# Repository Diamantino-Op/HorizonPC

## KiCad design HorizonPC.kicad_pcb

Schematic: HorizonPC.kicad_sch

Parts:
BT1: ML641; BAT_1376164-1
C1, C2, C3, C21, C22, C23, C111, C188, C189, C190, C191: 47u; C_0805_2012Metric
C4, C17, C18, C19, C20, C24, C106, C107, C108, C110: 22u; C_0805_2012Metric
C5: 470n; C_0402_1005Metric
C6: 220n; C_0402_1005Metric
C7, C8, C9, C10: 2.2u; C_0402_1005Metric
C11, C14, C15, C16, C37, C104, C109: 1u; C_0402_1005Metric
C12, C13: 12p; C_0402_1005Metric
C25, C30, C35, C36, C38, C39, C40, C41, C44, C63, C64, C94, C105, C117, C118, C128, C129, C130, C131, C132, C133, C134, C135, C136, C137, C138, C139, C140, C141, C143, C144, C145, C146, C147, C148, C149, C150, C151, C152, C153, C154, C155, C156, C157, C158, C159, C160, C161, C162, C163, C164, C165, C166, C167, C168, C169, C170, C171, C173, C174, C175, C176, C179, C180, C181, C182, C183, C184, C185, C192, C194, C210, C211, C212, C213, C214, C215, C216, C217, C219, C220, C221, C222, C223, C224, C225, C226: 100n; C_0402_1005Metric
C26: 1n; C_0402_1005Metric
C27, C28, C29, C31, C32, C34: 10u; C_0402_1005Metric
C33, C93, C186, C187: 4.7u; C_0402_1005Metric
C42, C43, C120: 4.7n; C_0402_1005Metric
C60, C61, C68, C70, C71, C72, C73, C74, C75, C76, C77, C81, C82, C83, C85, C88, C89, C90, C196, C197, C198, C199, C200, C201, C202, C203, C204, C205, C207: 47n; C_0402_1005Metric
C112, C113, C114, C115: 10u; C_0805_2012Metric
C116: 1u; C_0805_2012Metric
C119: 100p; C_0402_1005Metric
C121: 10n; C_0402_1005Metric
D1, D2: NUP2105L; SOT-23
D3: 12V; D_SOD-123
D4, D6: CDSOD323-T05S; D_SOD-323
D5: CDSOD323-T03S; D_SOD-323
F1: 8A; Fuse_0603_1608Metric
J2: MSD-1-A; CUI_MSD-1-A
J3: Conn_01x05_Pin; PinHeader_1x05_P1.00mm_Vertical
J4: DF40C-90DP-0.4V(51); HIROSE_DF40C-90DP-0.4V_51_
J5, J6: BK13H-30DP/2-0.35V05(895); BK13H-30DP_2-0.35V05
JP1: BSCANP Jumper; SolderJumper-2_P1.3mm_Open_RoundedPad1.0x1.5mm
JP2: DEBUGEN Jumper; SolderJumper-2_P1.3mm_Open_RoundedPad1.0x1.5mm
L1, L2: 1u; L_1008_2520Metric
L3, L4: 1u; L_Changjiang_FTC201607S
L5, L6: ACT45B-510-2P-TL003; FIL_ACT45B-510-2P-TL003
L7: 4.7u; L_Changjiang_FXL1050
Q1: PMOS; PowerPAK_SO-8_Single
R1: 200k; R_0402_1005Metric
R2, R3, R6, R7, R9, R10, R11, R18, R19, R20, R21, R22, R23, R24, R25, R26, R27, R28, R37, R39, R40, R78, R79, R80, R81, R83, R84, R85, R87, R89, R90, R91, R92, R93: 10k; R_0402_1005Metric
R4, R5: 4.7k; R_0402_1005Metric
R8, R69, R70, R72, R88: 100k; R_0402_1005Metric
R29, R30, R31, R32: 60; R_0402_1005Metric
R38: 100; R_0402_1005Metric
R41, R42, R66: 240; R_0402_1005Metric
R71: 49.9k; R_0402_1005Metric
R73: 31.6k; R_0402_1005Metric
R74: 8m; R_1206_3216Metric
R75, R76: 10; R_0402_1005Metric
R77: 15k; R_0402_1005Metric
R82: 22; R_0402_1005Metric
R86: 1.8k; R_0402_1005Metric
R94: 47k; R_0402_1005Metric
RN1, RN2, RN3, RN4, RN5, RN6, RN7: 49.9; RESCAXS50P200X100X55-8N
SW1: 219-5LPSTR; SW_DIP_SPSTx05_Slide_6.7x14.26mm_W6.73mm_P2.54mm_LowProfile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
TP1: TestPoint; TestPoint_Pad_D1.0mm
U1: R9A07G043F05GBG#BC0; Manufacturer_Part_Number R9A07G043F05GBG#BC0
U2: TPS51200DRC; VSON-10-1EP_3x3mm_P0.5mm_EP1.65x2.4mm
U3: S25FL256SAGNFI011; WDFN-8-1EP_8x6mm_P1.27mm_EP6x4.8mm
U4: DA9062-52AM1; VQFN-40-1EP_6x6mm_P0.5mm_EP3.5x3.5mm
U5, U6: ATA6561-GBQW-N; VDFN8_3X3_MCH
U7: SM662GXC; BGA-100_14x18mm_Layout10x17_P1mm
U8: PUSB3TB6AZ; XSON7_PUSB3_NEX
U9, U10: ECMF02-2AMX6; ST_UQFN-6L_1.5x1.7mm_P0.5mm
U11: TPS552892RYQR; CONV_TPS552892RYQR
U12: TPS2051CDBV; SOT-23-5
U14, U15: DDR4; FBGA-96_9x14mm_Layout9x16_P0.8mm
Y1: 32.768KHz; Crystal_SMD_MicroCrystal_CC8V-T1A-2Pin_2.0x1.2mm
Y2: DSC6101JE3B-24MHz; Oscillator_SMD_Abracon_ASDMB-4Pin_2.5x2.0mm

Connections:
+1.1V: C1.1, C21.1, C128.2, C129.2, C130.2, C131.2, C138.1, C140.1, C143.1, C144.1, C145.1, C146.1, C166.2, C186.1, L1.2, U1.K10 (VDD), U1.K12 (VDD), U1.K14 (VDD), U1.K16 (VDD), U1.L11 (VDD), U1.L13 (VDD), U1.L15 (VDD), U1.M10 (VDD), U1.M12 (VDD), U1.M14 (VDD), U1.M16 (VDD), U1.N11 (VDD), U1.N13 (VDD), U1.N15 (VDD), U1.P10 (VDD), U1.P12 (VDD), U1.P14 (VDD), U1.P16 (VDD), U1.R11 (VDD), U1.R13 (VDD), U1.R15 (VDD), U1.T6 (PLL23_DVDD11), U1.T10 (VDD), U1.T12 (VDD), U1.T14 (VDD), U1.T16 (VDD), U1.Y15 (PLL5_DVDD11), U4.26 (VBUCK1)
+1.2V: C2.1, C22.1, C31.2, C32.2, C60.2, C61.1, C68.2, C70.2, C71.1, C72.1, C73.1, C75.1, C76.2, C77.1, C81.2, C82.1, C83.2, C85.2, C171.1, C173.1, C174.1, C175.1, C176.1, C192.1, C194.1, C196.2, C197.1, C198.2, C199.1, C200.2, C201.1, C202.2, C203.2, C204.1, C205.2, C207.2, L2.2, R9.2, U1.H20 (DDR_VDDQ), U1.K20 (DDR_VDDQ), U1.M20 (DDR_VDDQ), U1.R20 (DDR_VDDQ), U1.U20 (DDR_VDDQ), U1.W20 (DDR_VDDQ), U2.2 (VLDOIN), U4.27 (VBUCK2), U14.A1 (V_{DDQ}), U14.A9 (V_{DDQ}), U14.B3 (V_{DD}), U14.B9 (V_{DD}), U14.C1 (V_{DDQ}), U14.D1 (V_{DD}), U14.D9 (V_{DDQ}), U14.F2 (V_{DDQ}), U14.F8 (V_{DDQ}), U14.G1 (V_{DDQ}), U14.G7 (V_{DD}), U14.G9 (V_{DDQ}), U14.J1 (V_{DD}), U14.J2 (V_{DDQ}), U14.J8 (V_{DDQ}), U14.J9 (V_{DD}), U14.L1 (V_{DD}), U14.L9 (V_{DD}), U14.R1 (V_{DD}), U14.T9 (V_{DD}), U15.A1 (V_{DDQ}), U15.A9 (V_{DDQ}), U15.B3 (V_{DD}), U15.B9 (V_{DD}), U15.C1 (V_{DDQ}), U15.D1 (V_{DD}), U15.D9 (V_{DDQ}), U15.F2 (V_{DDQ}), U15.F8 (V_{DDQ}), U15.G1 (V_{DDQ}), U15.G7 (V_{DD}), U15.G9 (V_{DDQ}), U15.J1 (V_{DD}), U15.J2 (V_{DDQ}), U15.J8 (V_{DDQ}), U15.J9 (V_{DD}), U15.L1 (V_{DD}), U15.L9 (V_{DD}), U15.R1 (V_{DD}), U15.T9 (V_{DD})
+1.8V: C4.1, C24.1, C44.1, C132.1, C133.1, C134.2, C135.2, C136.1, C137.2, C141.1, C150.1, C151.1, C163.1, C219.2, C220.1, C221.2, C222.1, C223.2, C224.1, C225.2, C226.1, L4.2, U1.AC4 (USB_VDD18), U1.AC5 (USB_VDD18), U1.AC9 (USB_VDD18), U1.F11 (PLL6_AVDD18), U1.F17 (ADC_AVDD18), U1.G3 (SD0_PVDD), U1.L3 (PLL1_AVDD18), U1.N17 (PLL4_AVDD18), U1.P6 (VDD18), U1.U3 (PLL23_AVDD18), U1.Y11 (CSI_VDD18), U1.Y12 (CSI_VDD18), U1.Y14 (PLL5_AVDD18), U4.24 (VBUCK4), U7.H3 (VCCQ), U7.H8 (VCCQ), U7.L2 (VCCQ), U7.L4 (VCCQ), U7.L7 (VCCQ), U7.L9 (VCCQ), U7.P3 (VCCQ), U7.P8 (VCCQ)
+3.3V: C3.1, C23.1, C25.1, C33.1, C34.1, C35.1, C38.2, C40.2, C139.2, C160.1, C161.1, C164.1, C179.1, C180.1, C181.1, C182.1, C183.1, C184.1, C185.1, C187.2, C210.2, C211.2, C212.2, C213.2, C214.1, C215.1, C216.1, C217.1, JP2.2 (B), L3.2, R3.1, R4.1, R5.1, R7.1, R8.1, R11.1, R18.1, R79.1, R80.1, R81.1, R83.1, R87.1, R89.1, R90.1, R91.1, R92.1, R93.1, SW1.6, SW1.7, SW1.8, SW1.9, SW1.10, U1.C8 (SPI_PVDD), U1.C19 (PVDD), U1.F9 (PVDD), U1.F13 (PVDD), U1.F19 (PVDD), U1.W6 (PVDD), U1.Y7 (USB_VDD33), U1.Y8 (USB_VDD33), U1.Y10 (PVDD), U1.Y17 (PVDD_ETH1), U1.Y18 (PVDD), U2.7 (EN), U2.10 (VIN), U3.8 (VCC), U4.23 (VDDIO), U4.25 (VBUCK3), U5.5 (VIO), U6.5 (VIO), U7.F2 (VCC), U7.F3 (VCC), U7.F4 (VCC), U7.F5 (VCC), U7.F6 (VCC), U7.F7 (VCC), U7.F8 (VCC), U7.F9 (VCC), Y2.4 (VDD)
+5V: C14.1, C15.1, C16.1, C17.1, C18.1, C19.1, C20.1, C39.2, C41.2, C109.2, C155.2, D6.1 (A1), J6.8b, J6.9a, J6.9b, J6.10a, J6.10b, J6.11a, J6.11b, R2.1, R6.1, R72.1, R74.2, R76.2, U4.3 (VDD_LDO2), U4.10 (VDD_LDO34), U4.18 (VDD_BUCK4), U4.19 (VDD_BUCK3), U4.32 (VDD_BUCK1), U4.33 (VDD_BUCK2), U4.40 (VSYS), U5.3 (VCC), U6.3 (VCC), U12.5 (IN)
+5V_EXT: U1.AD8 (USB0_VBUSIN)
+5V_USB: C188.1, C189.1, C190.1, C191.1, D4.1 (A1), J6.5a, J6.5b, J6.6a, J6.6b, J6.7a, J6.7b, J6.8a, U12.1 (OUT)
ADC_CH0_ARM: J5.14a, U1.B18 (ADC_CH0)
ADC_CH1_ARM: J5.15a, U1.A18 (ADC_CH1)
ADC_TRG: U1.AC17 (ADC_TRG)
AUDIO_BCK: U1.AD18 (SSI3_BCK)
AUDIO_MCK: J5.4a, U1.B8 (AUDIO_CLK2)
AUDIO_RCK: U1.AC20 (SSI3_RCK)
AUDIO_RXD: U1.AC19 (SSI3_RXD)
AUDIO_TXD: U1.AE21 (SSI3_TXD)
BOOT0: R28.1, SW1.1, U1.G6 (MD_BOOT0)
BOOT1: R27.1, SW1.2, U1.C5 (MD_BOOT1)
BOOT2: R26.1, SW1.3, U1.C4 (MD_BOOT2)
CAN0_CANH: D1.2 (K), J4.45a, L6.4
CAN0_CANL: D1.1 (K), J4.44a, L6.2
CAN0_RXD: U1.C12 (CAN0_RX), U5.4 (RXD)
CAN0_STBY: R37.1, U1.AC15 (P8_3), U5.8 (STBY)
CAN0_TXD: U1.A11 (CAN0_TX), U5.1 (TXD)
CAN1_CANH: D2.2 (K), J4.45b, L5.4
CAN1_CANL: D2.1 (K), J4.44b, L5.2
CAN1_RXD: U1.B13 (CAN1_RX), U6.4 (RXD)
CAN1_STBY: R40.1, U1.AC16 (P8_2), U6.8 (STBY)
CAN1_TXD: U1.C13 (CAN1_TX), U6.1 (TXD)
CSI_CLK+: J4.29a, U1.AD11 (CSI_CLK+)
CSI_CLK-: J4.28a, U1.AE11 (CSI_CLK-)
CSI_D0+: J4.32a, U1.AD12 (CSI_D0+)
CSI_D0-: J4.31a, U1.AE12 (CSI_D0-)
CSI_D1+: J4.26a, U1.AD10 (CSI_D1+)
CSI_D1-: J4.25a, U1.AE10 (CSI_D1-)
CSI_D2+: J4.35a, U1.AD13 (ADC_CH1)
CSI_D2-: J4.34a, U1.AE13 (ADC_CH0)
CSI_D3+: J4.22a, U1.AD9 (CSI_D3+)
CSI_D3-: J4.23a, U1.AE9 (CSI_D3-)
DDR_A0: RN4.1 (R1.1), U1.H25 (DDR_ADDR11), U14.P3 (A0), U15.P3 (A0)
DDR_A1: RN2.3 (R3.1), U1.C24 (DDR_ADDR3), U14.P7 (A1), U15.P7 (A1)
DDR_A2: RN2.1 (R1.1), U1.E24 (DDR_BA0), U14.R3 (A2), U15.R3 (A2)
DDR_A3: RN3.4 (R4.1), U1.D23 (DDR_ADDR13), U14.N7 (A3), U15.N7 (A3)
DDR_A4: RN4.4 (R4.1), U1.J24 (DDR_CAS#), U14.N3 (A4), U15.N3 (A4)
DDR_A5: RN2.2 (R2.1), U1.D25 (DDR_ADDR15), U14.P8 (A5), U15.P8 (A5)
DDR_A6: RN2.4 (R4.1), U1.H24 (DDR_RAS#), U14.P2 (A6), U15.P2 (A6)
DDR_A7: RN1.3 (R3.1), U1.C25 (DDR_ADDR2), U14.R8 (A7), U15.R8 (A7)
DDR_A8: RN3.3 (R3.1), U1.H23 (DDR_ADDR14), U14.R2 (A8), U15.R2 (A8)
DDR_A9: RN1.4 (R4.1), U1.B24 (DDR_ADDR9), U14.R7 (A9), U15.R7 (A9)
DDR_A10: RN4.3 (R3.1), U1.F23 (DDR_BA2), U14.M3 (A10/AP), U15.M3 (A10/AP)
DDR_A11: RN1.2 (R2.1), U1.A24 (DDR_ADDR7), U14.T2 (A11), U15.T2 (A11)
DDR_A12: RN5.4 (R4.1), U1.G25 (DDR_WE#), U14.M7 (A12/~BC), U15.M7 (A12/~BC)
DDR_A13: RN1.1 (R1.1), U1.B25 (DDR_ADDR5), U14.T8 (A13), U15.T8 (A13)
DDR_ACT: RN6.3 (R3.1), U1.L25 (DDR_ODT1), U14.L3 (~ACT), U15.L3 (~ACT)
DDR_BA0: RN3.1 (R1.1), U1.J25 (DDR_ADDR6), U14.N2 (BA0), U15.N2 (BA0)
DDR_BA1: RN3.2 (R2.1), U1.E25 (DDR_ADDR0), U14.N8 (BA1), U15.N8 (BA1)
DDR_BG0: RN6.2 (R2.1), U1.N23 (DDR_ADDR12), U14.M2 (BG0), U15.M2 (BG0)
DDR_CAS: RN4.2 (R2.1), U1.F25 (DDR_ADDR8), U14.M8 (A15/~CAS), U15.M8 (A15/~CAS)
DDR_CK+: R38.1, U1.P25 (DDR_CLK_P), U14.K7 (CK_t), U15.K7 (CK_t)
DDR_CK-: R38.2, U1.P24 (DDR_CLK_N), U14.K8 (CK_c), U15.K8 (CK_c)
DDR_CKE: RN7.2 (R2.1), U1.M25 (DDR_CKE), U14.K2 (CKE), U15.K2 (CKE)
DDR_CS0: RN5.1 (R1.1), U1.L24 (DDR_BA1), U14.L7 (~CS)
DDR_CS1: RN5.2 (R2.1), U1.M24 (DDR_ODT0), U15.L7 (~CS)
DDR_DQ0: U1.W24 (DDR_DQ1), U14.G2 (DQ0), U15.G2 (DQ0)
DDR_DQ1: U1.Y25 (DDR_DQ3), U14.F7 (DQ1), U15.F7 (DQ1)
DDR_DQ2: U1.T23 (DDR_DQ7), U14.H3 (DQ2), U15.H3 (DQ2)
DDR_DQ3: U1.U25 (DDR_DQ5), U14.H7 (DQ3), U15.H7 (DQ3)
DDR_DQ4: U1.T24 (DDR_DQ4), U14.H2 (DQ4), U15.H2 (DQ4)
DDR_DQ5: U1.T25 (DDR_DQ0), U14.H8 (DQ5), U15.H8 (DQ5)
DDR_DQ6: U1.R24 (DDR_DQ2), U14.J3 (DQ6), U15.J3 (DQ6)
DDR_DQ7: U1.R25 (DDR_DQ6), U14.J7 (DQ7), U15.J7 (DQ7)
DDR_DQ8: U1.AD23 (DDR_DQ12), U14.A3 (DQ8), U15.A3 (DQ8)
DDR_DQ9: U1.AE24 (DDR_DQ15), U14.B8 (DQ9), U15.B8 (DQ9)
DDR_DQ10: U1.AC24 (DDR_DQ14), U14.C3 (DQ10), U15.C3 (DQ10)
DDR_DQ11: U1.AD24 (DDR_DQ8), U14.C7 (DQ11), U15.C7 (DQ11)
DDR_DQ12: U1.AA23 (DDR_DQ13), U14.C2 (DQ12), U15.C2 (DQ12)
DDR_DQ13: U1.AD25 (DDR_DQ11), U14.C8 (DQ13), U15.C8 (DQ13)
DDR_DQ14: U1.AA24 (DDR_DQ9), U14.D3 (DQ14), U15.D3 (DQ14)
DDR_DQ15: U1.W23 (DDR_DQ10), U14.D7 (DQ15), U15.D7 (DQ15)
DDR_LDM: U1.U23 (DDR_DM0), U14.E7 (NF/~LDM/~LDBI), U15.E7 (NF/~LDM/~LDBI)
DDR_LDQS+: U1.V25 (DDR_DQS0_P), U14.G3 (LDQS_t), U15.G3 (LDQS_t)
DDR_LDQS-: U1.V24 (DDR_DQS0_N), U14.F3 (LDQS_c), U15.F3 (LDQS_c)
DDR_ODT0: RN5.3 (R3.1), U1.L23 (DDR_CS1#), U14.K3 (ODT)
DDR_ODT1: RN6.4 (R4.1), U1.N24 (DDR_CS0#), U15.K3 (ODT)
DDR_PWR_GOOD: R8.2, U2.9 (PGOOD)
DDR_RAS: RN6.1 (R1.1), U1.K25 (DDR_ADDR1), U14.L8 (A16/~RAS), U15.L8 (A16/~RAS)
DDR_RESET#: R39.1, U1.B23 (DDR_RESET#), U14.P1 (~RESET), U15.P1 (~RESET)
DDR_UDM: U1.Y24 (DDR_DM1), U14.E2 (NF/~UDM/~UDBI), U15.E2 (NF/~UDM/~UDBI)
DDR_UDQS+: U1.AB24 (DDR_DQS1_P), U14.B7 (UDQS_t), U15.B7 (UDQS_t)
DDR_UDQS-: U1.AB25 (DDR_DQS1_N), U14.A7 (UDQS_c), U15.A7 (UDQS_c)
DDR_WE: RN7.1 (R1.1), U1.K23 (DDR_ADDR4), U14.L2 (A14/~WE), U15.L2 (A14/~WE)
ETH_MDC: J4.9a, U1.T3 (ET0_MDC)
ETH_MDIO: J4.10a, U1.T2 (ET0_MDIO)
ETH_RXC: J4.18a, U1.N3 (ET0_RXC)
ETH_RXD0: J4.16a, U1.P2 (ET0_RXD0)
ETH_RXD1: J4.15a, U1.R3 (ET0_RXD1)
ETH_RXD2: J4.13a, U1.R2 (ET0_RXD2)
ETH_RXD3: J4.12a, U1.R1 (ET0_RXD3)
ETH_RX_CTL: J4.20a, U1.N1 (ET0_RX_CTL)
ETH_TXC: J4.18b, U1.M2 (ET0_TXC)
ETH_TXD0: J4.16b, U1.L1 (ET0_TXD0)
ETH_TXD1: J4.15b, U1.L2 (ET0_TXD1)
ETH_TXD2: J4.13b, U1.K1 (ET0_TXD2)
ETH_TXD3: J4.12b, U1.K2 (ET0_TXD3)
ETH_TX_CTL: J4.20b, U1.M1 (ET0_TX_CTL)
GND: BT1.2 (-), C1.2, C2.2, C3.2, C4.2, C5.2, C6.2, C7.2, C8.2, C9.2, C10.2, C11.2, C12.2, C13.2, C14.2, C15.2, C16.2, C17.2, C18.2, C19.2, C20.2, C21.2, C22.2, C23.2, C24.2, C25.2, C26.2, C27.2, C28.2, C29.2, C30.2, C31.1, C32.1, C33.2, C34.2, C35.2, C36.2, C37.2, C38.1, C39.1, C40.1, C41.1, C42.2, C43.2, C44.2, C60.1, C61.2, C68.1, C70.1, C71.2, C72.2, C73.2, C74.2, C75.2, C76.1, C77.2, C81.1, C82.2, C83.1, C85.1, C88.2, C89.2, C90.2, C93.2, C94.2, C104.1, C105.1, C106.1, C107.1, C108.1, C109.1, C110.1, C111.1, C112.1, C113.1, C114.1, C115.1, C116.1, C117.1, C119.2, C120.1, C121.2, C128.1, C129.1, C130.1, C131.1, C132.2, C133.2, C134.1, C135.1, C136.2, C137.1, C138.2, C139.1, C140.2, C141.2, C143.2, C144.2, C145.2, C146.2, C147.2, C148.2, C149.2, C150.2, C151.2, C152.2, C153.2, C154.1, C155.1, C156.1, C157.1, C158.1, C159.1, C160.2, C161.2, C162.2, C163.2, C164.2, C165.2, C166.1, C167.1, C168.2, C169.1, C170.2, C171.2, C173.2, C174.2, C175.2, C176.2, C179.2, C180.2, C181.2, C182.2, C183.2, C184.2, C185.2, C186.2, C187.1, C188.2, C189.2, C190.2, C191.2, C196.1, C197.2, C198.1, C199.2, C200.1, C201.2, C202.1, C203.1, C204.2, C205.1, C207.1, C210.1, C211.1, C212.1, C213.1, C214.2, C215.2, C216.2, C217.2, C219.1, C220.2, C221.1, C222.2, C223.1, C224.2, C225.1, C226.2, D1.3 (A), D2.3 (A), D4.2 (A2), D5.2 (A2), D6.2 (A2), J2.6 (VSS), J2.G1 (SHIELD), J2.G2 (SHIELD), J2.G3 (SHIELD), J2.G4 (SHIELD), J4.5a, J4.11a, J4.11b, J4.14a, J4.14b, J4.17a, J4.17b, J4.19a, J4.19b, J4.21a, J4.21b, J4.24a, J4.27a, J4.30a, J4.33a, J4.36a, J4.38a, J4.43a, J4.43b, J4.MP (MountPin), J5.P1 (MountPin), J5.P2 (MountPin), J6.12a, J6.12b, J6.13a, J6.13b, J6.14a, J6.14b, J6.15a, J6.15b, J6.P2 (MountPin), JP1.2 (B), R1.2, R10.2, R24.2, R25.2, R26.2, R27.2, R28.2, R37.2, R39.2, R40.2, R41.2, R42.2, R66.2, R69.2, R71.2, R73.2, R78.2, R84.2, R85.2, R86.1, R88.2, R94.2, U1.A1 (VSS), U1.A8 (VSS), U1.A25 (VSS), U1.AA3 (VSS), U1.AA25 (VSS), U1.AB1 (VSS), U1.AB23 (VSS), U1.AC6 (VSS), U1.AC7 (VSS), U1.AC10 (VSS), U1.AC11 (VSS), U1.AC12 (VSS), U1.AC13 (VSS), U1.AC14 (VSS), U1.AC21 (VSS), U1.AC22 (VSS), U1.AC23 (VSS), U1.AC25 (VSS), U1.AD4 (VSS), U1.AD7 (VSS), U1.AD14 (VSS), U1.AD21 (VSS), U1.AD22 (VSS), U1.AE1 (VSS), U1.AE4 (VSS), U1.AE7 (VSS), U1.AE8 (VSS), U1.AE14 (VSS), U1.AE23 (VSS), U1.AE25 (VSS), U1.C18 (VSS), U1.C22 (VSS), U1.C23 (VSS), U1.D24 (VSS), U1.E23 (VSS), U1.F6 (VSS), U1.F7 (VSS), U1.F8 (VSS), U1.F10 (VSS), U1.F12 (VSS), U1.F15 (VSS), U1.F18 (VSS), U1.F24 (VSS), U1.G20 (VSS), U1.G23 (VSS), U1.G24 (VSS), U1.H1 (VSS), U1.J6 (VSS), U1.J9 (VSS), U1.J11 (VSS), U1.J13 (VSS), U1.J15 (VSS), U1.J17 (VSS), U1.J20 (VSS), U1.J23 (VSS), U1.K24 (VSS), U1.L6 (VSS), U1.L9 (VSS), U1.L17 (VSS), U1.L20 (VSS), U1.M23 (VSS), U1.N6 (VSS), U1.N9 (VSS), U1.N20 (VSS), U1.N25 (VSS), U1.P20 (VSS), U1.R6 (VSS), U1.R9 (VSS), U1.R17 (VSS), U1.R23 (VSS), U1.T1 (VSS), U1.T20 (VSS), U1.U6 (VSS), U1.U9 (VSS), U1.U11 (VSS), U1.U13 (VSS), U1.U15 (VSS), U1.U17 (VSS), U1.U24 (VSS), U1.V3 (VSS), U1.V6 (VSS), U1.V20 (VSS), U1.V23 (VSS), U1.W3 (VSS), U1.W25 (VSS), U1.Y1 (VSS), U1.Y2 (XIN), U1.Y6 (VSS), U1.Y9 (VSS), U1.Y13 (VSS), U1.Y16 (VSS), U1.Y20 (VSS), U1.Y23 (VSS), U2.4 (GND), U2.8 (GND), U2.11 (GND), U3.4 (GND), U3.9 (GND), U4.7 (GND), U4.41 (GND), U5.2 (GND), U5.9 (GND), U6.2 (GND), U6.9 (GND), U7.G2 (VSS), U7.G3 (VSS), U7.G4 (VSS), U7.G5 (VSS), U7.G6 (VSS), U7.G7 (VSS), U7.G8 (VSS), U7.G9 (VSS), U7.H2 (VSSQ), U7.H9 (VSSQ), U7.J5 (VSS), U7.L3 (VSSQ), U7.L8 (VSSQ), U7.M4 (VSSQ), U7.M7 (VSSQ), U7.P2 (VSSQ), U7.P9 (VSSQ), U8.1 (GND), U9.3 (GND), U10.3 (GND), U11.9 (GND), U11.17 (GND), U12.2 (GND), U14.A2 (V_{SSQ}), U14.A8 (V_{SSQ}), U14.B2 (V_{SS}), U14.C9 (V_{SSQ}), U14.D2 (V_{SSQ}), U14.D8 (V_{SSQ}), U14.E1 (V_{SS}), U14.E3 (V_{SSQ}), U14.E8 (V_{SSQ}), U14.E9 (V_{SS}), U14.F1 (V_{SSQ}), U14.G8 (V_{SS}), U14.H1 (V_{SSQ}), U14.H9 (V_{SSQ}), U14.K1 (V_{SS}), U14.K9 (V_{SS}), U14.M9 (V_{SS}), U14.N1 (V_{SS}), U14.T1 (V_{SS}), U15.A2 (V_{SSQ}), U15.A8 (V_{SSQ}), U15.B2 (V_{SS}), U15.C9 (V_{SSQ}), U15.D2 (V_{SSQ}), U15.D8 (V_{SSQ}), U15.E1 (V_{SS}), U15.E3 (V_{SSQ}), U15.E8 (V_{SSQ}), U15.E9 (V_{SS}), U15.F1 (V_{SSQ}), U15.G8 (V_{SS}), U15.H1 (V_{SSQ}), U15.H9 (V_{SSQ}), U15.K1 (V_{SS}), U15.K9 (V_{SS}), U15.M9 (V_{SS}), U15.N1 (V_{SS}), U15.T1 (V_{SS}), Y2.2 (GND)
GPIO0_33: J4.37a, U1.AE15 (P8_0)
GPIO0_1833: U1.K6 (P2_1)
GPIO1_33: J5.7a, U1.B17 (P18_2)
GPIO1_1833: U1.M3 (P2_2)
GPIO2_33: J5.11a, U1.A17 (P18_1)
GPIO2_1833: U1.M6 (P2_3)
GPIO3_33: J5.4b, U1.F16 (P18_0)
GPIO3_1833: U1.N2 (P4_2)
GPIO4_33: J5.8a, U1.C20 (P18_3)
GPIO4_1833: U1.P1 (P4_5)
GPIO5_33: J5.3b, U1.B12 (P13_3)
GPIO6_33: J5.6a, U1.A4 (P24_1)
GPIO7_33: J5.10a, U1.A14 (P16_0)
GPIO8_33: J5.9a, U1.B14 (P16_1)
GPIO9_33: J5.2b, U1.A12 (P13_4)
IRQ0: J5.12a, U1.A13 (IRQ3)
IRQ1: U1.AD20 (IRQ4)
IRQ2: U1.AE18 (IRQ5)
IRQ3: J5.13a, U1.B22 (IRQ6)
IRQ4: J5.15b, U1.A21 (IRQ7)
JTAG_TCK: J3.2, J4.4b, U1.U2 (TCK/SWDCLK)
JTAG_TDI: J3.5, J4.1b, U1.W1 (TDI)
JTAG_TDO: J3.4, J4.2b, U1.V2 (TDO)
JTAG_TMS: J3.1, J4.5b, U1.U1 (TMS/SWDIO)
JTAG_TRST#: J3.3, J4.3b, U1.V1 (TRST#)
LDO2_EN: U1.B3 (P24_4), U4.22 (GPIO1)
LDO3_EN: U1.A3 (P24_3), U4.28 (GPIO2)
LDO4_EN: U1.B4 (P24_2), U4.29 (GPIO3)
MAIN_RESET: J4.8a, R6.2, U4.16 (~RESETREQ)
MAIN_SCL: J5.13b, U1.B19 (RIIC0_SCL)
MAIN_SDA: J5.14b, U1.B20 (RIIC0_SDA)
MTU0_A: U1.AC18 (MTU4_A)
MTU0_AB_DIS#: J5.3a, R91.2, U1.B9 (POE0#)
MTU0_B: U1.AE19 (MTU4_B)
MTU0_C: U1.AD19 (MTU4_C)
MTU0_CD_DIS#: J5.2a, R89.2, U1.C9 (POE4#)
MTU0_D: U1.AE20 (MTU4_D)
MTU1_A: J4.10b, U1.AD3 (MTU7_A)
MTU1_AB_DIS#: J5.1a, R92.2, U1.B10 (POE8#)
MTU1_B: J4.9b, U1.AC3 (MTU7_B)
MTU1_C: J4.8b, U1.AB2 (MTU7_C)
MTU1_CD_DIS#: J5.1b, R90.2, U1.A10 (POE10#)
MTU1_D: J4.7b, U1.AC1 (MTU7_D)
NMI: J4.6b, U1.AA2 (NMI)
unnamed: BT1.1 (+), C5.1, U4.12 (VBBAT)
unnamed: C42.1, R29.2, R30.1
unnamed: C43.1, R31.2, R32.1
unnamed: C120.2, R77.2
unnamed: D3.2 (A), Q1.2 (G), R94.1
unnamed: D3.1 (K), F1.1, Q1.3 (S)
unnamed: JP1.1 (A), R79.2, U1.Y19 (DEBUGEN)
unnamed: JP2.1 (A), R78.1, U1.AE22 (BSCANP)
unnamed: L2.1, U4.34 (VLX_BUCK2), U4.35 (VLX_BUCK2)
unnamed: R82.2, U1.Y3 (EXCLK)
unnamed: R81.2, U1.F20 (MD_CLKS)
unnamed: R85.1, U1.A22 (MD_OSCDRV0)
unnamed: R84.1, U1.C21 (MD_OSCDRV1)
unnamed: R66.1, U1.A23 (DDR_CALIBRATION)
unnamed: R86.2, U1.AC8 (USB_RREF)
unnamed: C26.1, R9.1, R10.1, U2.1 (REFIN)
unnamed: R1.1, U4.4 (IREF)
unnamed: TP1.1 (1_1), U4.36 (TP)
unnamed: C7.1, U4.39 (VDDCORE)
unnamed: L1.1, U4.31 (VLX_BUCK1)
unnamed: L3.1, U4.20 (VLX_BUCK3)
unnamed: L4.1, U4.17 (VLX_BUCK4)
unnamed: C6.1, U4.5 (VREF)
unnamed: C13.1, U4.6 (XTAL_IN), Y1.2
unnamed: C12.1, U4.8 (XTAL_OUT), Y1.1
unnamed: L6.3, R31.1, U5.7 (CANH)
unnamed: L6.1, R32.2, U5.6 (CANL)
unnamed: L5.3, R29.1, U6.7 (CANH)
unnamed: L5.1, R30.2, U6.6 (CANL)
unnamed: C37.1, U7.E4 (VDDI)
unnamed: C63.1, U11.20 (BOOT1)
unnamed: C64.1, U11.19 (BOOT2)
unnamed: C119.1, R77.1, U11.15 (COMP)
unnamed: R72.2, R73.1, U11.14 (FB)
unnamed: R71.1, U11.6 (FSW)
unnamed: C118.2, R76.1, U11.13 (ISN)
unnamed: C118.1, R75.1, U11.12 (ISP)
unnamed: R70.1, U11.2 (MODE)
unnamed: C63.2, L7.1, U11.8 (SW1)
unnamed: C64.2, L7.2, U11.10 (SW2)
unnamed: C121.1, U11.5 (SYNC)
unnamed: C93.1, C94.1, R70.2, U11.18 (VCC)
unnamed: C104.2, C105.2, C106.2, C107.2, C108.2, C110.2, C111.2, R74.1, R75.2, U11.11 (VOUT)
unnamed: R41.1, U14.F9 (ZQ)
unnamed: R42.1, U15.F9 (ZQ)
unnamed: R82.1, Y2.3 (Out)
unnamed: R83.2, Y2.1 (Standby)
PWR_CC: R80.2, U1.C11 (IRQ1), U11.4 (~CC)
PWR_GOOD: R93.2, U1.AD15 (IRQ2), U11.3 (PG)
PWR_IRQ: R3.2, U1.C10 (IRQ0), U4.37 (~IRQ)
PWR_ONKEY: J4.6a, R2.2, U4.15 (~ONKEY)
PWR_RESET: R7.2, U1.W2 (PRST#), U4.38 (~RESET)
PWR_SCL: R4.2, U1.A19 (RIIC1_SCL), U4.14 (SCL)
PWR_SDA: R5.2, U1.A20 (RIIC1_SDA), U4.13 (SDA)
PWR_WDT: U1.B2 (P24_0), U4.21 (GPIO0)
PWR_WDT_ERR: J5.5a, U1.A2 (WDT)
QSPI_CS: R11.2, U1.B5 (QSPI0_SSL), U3.1 (~CS)
QSPI_IO0: U1.C7 (QSPI0_IO0), U3.5 (IO0)
QSPI_IO1: U1.A5 (QSPI0_IO1), U3.2 (IO1)
QSPI_IO2: U1.B7 (QSPI0_IO2), U3.3 (IO2)
QSPI_IO3: U1.C6 (QSPI0_IO3), U3.7 (IO3)
QSPI_SCK: U1.B6 (QSPI0_SPCLK), U3.6 (SCK)
SD0_CLK: U1.G1 (SD0_CLK), U7.P6 (CLK)
SD0_CMD: U1.E2 (SD0_CMD), U7.P5 (CMD)
SD0_D0: U1.F1 (SD0_DATA0), U7.K2 (D0)
SD0_D1: U1.H3 (SD0_DATA1), U7.N2 (D1)
SD0_D2: U1.F2 (SD0_DATA2), U7.K3 (D2)
SD0_D3: U1.D2 (SD0_DATA3), U7.N3 (D3)
SD0_D4: U1.E1 (SD0_DATA4), U7.N8 (D4)
SD0_D5: U1.D1 (SD0_DATA5), U7.K8 (D5)
SD0_D6: U1.E3 (SD0_DATA6), U7.N9 (D6)
SD0_D7: U1.F3 (SD0_DATA7), U7.K9 (D7)
SD0_WP: R25.1, SW1.4, U1.C2 (SD0_WP)
SD0_~RST: U1.C1 (SD0_RST#), U7.M5 (RST#)
SD1_CLK: J2.5 (CLK), U1.G2 (SD1_CLK), U8.3 (CH2)
SD1_CMD: J2.3 (CMD), R21.2, U1.H6 (SD1_CMD), U8.6 (CH5)
SD1_D0: J2.7 (DAT0), R20.2, U1.H2 (SD1_DATA0), U8.5 (CH4)
SD1_D1: J2.8 (DAT1), R19.2, U1.J3 (SD1_DATA1), U8.4 (CH3)
SD1_D2: J2.1 (DAT2), R23.2, U1.J1 (SD1_DATA2), U8.7 (CH6)
SD1_D3: J2.2 (DAT3/CD), R22.2, U1.J2 (SD1_DATA3), U8.2 (CH1)
SD1_DET: J2.CD (DET), R18.2, U1.D3 (SD1_CD)
SD1_WP: R24.1, SW1.5, U1.C3 (SD1_WP)
SERIAL_CTS: U1.AD2 (SCIF2_CTS)
SERIAL_RTS: U1.AC2 (SCIF2_RTS)
SERIAL_RXD: U1.AE2 (SCIF2_RXD)
SERIAL_SCK: U1.AE3 (SCIF2_SCK)
SERIAL_TXD: U1.AD1 (SCIF2_TXD)
SPI0_CLK: J5.8b, U1.C14 (RSPI0_CLK)
SPI0_MISO: J5.6b, U1.B15 (RSPI0_MISO)
SPI0_MOSI: J5.7b, U1.C15 (RSPI0_MOSI)
SPI0_SSL: J5.5b, U1.A15 (RSPI0_SSL)
SPI1_CLK: J5.12b, U1.C16 (RSPI1_CLK)
SPI1_MISO: J5.10b, U1.A16 (RSPI1_MISO)
SPI1_MOSI: J5.11b, U1.B16 (RSPI1_MOSI)
SPI1_SSL: J5.9b, U1.C17 (RSPI1_SSL)
SPI2_CLK: J4.41a, U1.AE17 (RSPI2_CLK)
SPI2_MISO: J4.39a, U1.AD16 (RSPI2_MISO)
SPI2_MOSI: J4.42a, U1.AD17 (RSPI2_MOSI)
SPI2_SSL: J4.40a, U1.AE16 (RSPI2_SSL)
SYS_EN: J4.7a, R69.1, U4.30 (GPIO4), U11.1 (EN)
USB+: U1.AD5 (USB1_DP), U9.1 (D+_in)
USB-: U1.AE5 (USB1_DM), U9.2 (D-_in)
USB_EN: R88.1, U1.B11 (USB1_VBUSEN), U12.4 (EN)
USB_ESD+: J4.1a, U9.6 (D+_out)
USB_ESD-: J4.2a, U9.5 (D-_out)
USB_FLT: R87.2, U1.AB3 (USB1_OVRCUR), U12.3 (~FLT)
USB_MAIN+: U1.AD6 (USB0_DP), U10.2 (D-_in)
USB_MAIN-: U1.AE6 (USB0_DM), U10.1 (D+_in)
USB_MAIN_ESD+: J4.4a, U10.5 (D-_out)
USB_MAIN_ESD-: J4.3a, U10.6 (D+_out)
VETH: C8.1, C165.1, U1.P3 (PVDD_ETH0), U4.2 (VLDO2)
VGPIO: C9.1, U4.11 (VLDO4)
VMAIN: C112.2, C113.2, C114.2, C115.2, C116.2, C117.2, F1.2, U11.7 (VIN)
VMAIN_RAW: J6.1a, J6.1b, J6.2a, J6.2b, J6.3a, J6.3b, J6.4a, J6.4b, J6.P1 (MountPin), Q1.1 (D)
VPP: C11.1, C74.1, C88.1, C89.1, C90.1, U4.1 (VLDO1), U14.B1 (V_{PP}), U14.R9 (V_{PP}), U15.B1 (V_{PP}), U15.R9 (V_{PP})
VSD1: C10.1, C36.1, C162.1, D5.1 (A1), J2.4 (VDD), R19.1, R20.1, R21.1, R22.1, R23.1, U1.K3 (SD1_PVDD), U4.9 (VLDO3)
VTT: C27.1, C28.1, C29.1, C147.1, C148.1, C149.1, C152.1, C153.1, C154.2, C156.2, C157.2, C158.2, C159.2, C167.2, C168.1, C169.2, C170.1, RN1.5 (R4.2), RN1.6 (R3.2), RN1.7 (R2.2), RN1.8 (R1.2), RN2.5 (R4.2), RN2.6 (R3.2), RN2.7 (R2.2), RN2.8 (R1.2), RN3.5 (R4.2), RN3.6 (R3.2), RN3.7 (R2.2), RN3.8 (R1.2), RN4.5 (R4.2), RN4.6 (R3.2), RN4.7 (R2.2), RN4.8 (R1.2), RN5.5 (R4.2), RN5.6 (R3.2), RN5.7 (R2.2), RN5.8 (R1.2), RN6.5 (R4.2), RN6.6 (R3.2), RN6.7 (R2.2), RN6.8 (R1.2), RN7.5 (R4.2), RN7.6 (R3.2), RN7.7 (R2.2), RN7.8 (R1.2), U2.3 (VO), U2.5 (VOSNS)
VTT_REF: C30.1, C192.2, C194.2, U2.6 (REFOUT), U14.M1 (V_{REFCA}), U15.M1 (V_{REFCA})

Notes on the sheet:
Main Power -> 5V
USB
MPU DDR4
Power
CAN1
QSPI
DDR4 Terminations
MPU CSI
MPU MTU
Reverse Polarity
DDR4 Bank 1
MPU USB
A18 / B18 only active with G2UL AD13 / AE13 only active with Rz/Five
To LEDs
MPU ADC
MPU GPIO
MPU Serial
DDR Terminations
USB ESD
MicroSD
DDR3L
MPU QSPI
MPU I2C
To Connector
CAN0
MPU Ethernet
Main USB ESD
MPU Clocks
MPU MicroSD
JTAG Connector
MPU Power
MPU Interrupts
Switches
MPU JTAG
DDR4 Bank 0
CAN
PMIC
MPU SPI
With G2UL: AE13 = CSI_D2- AD13 = CSI_D2+
eMMC

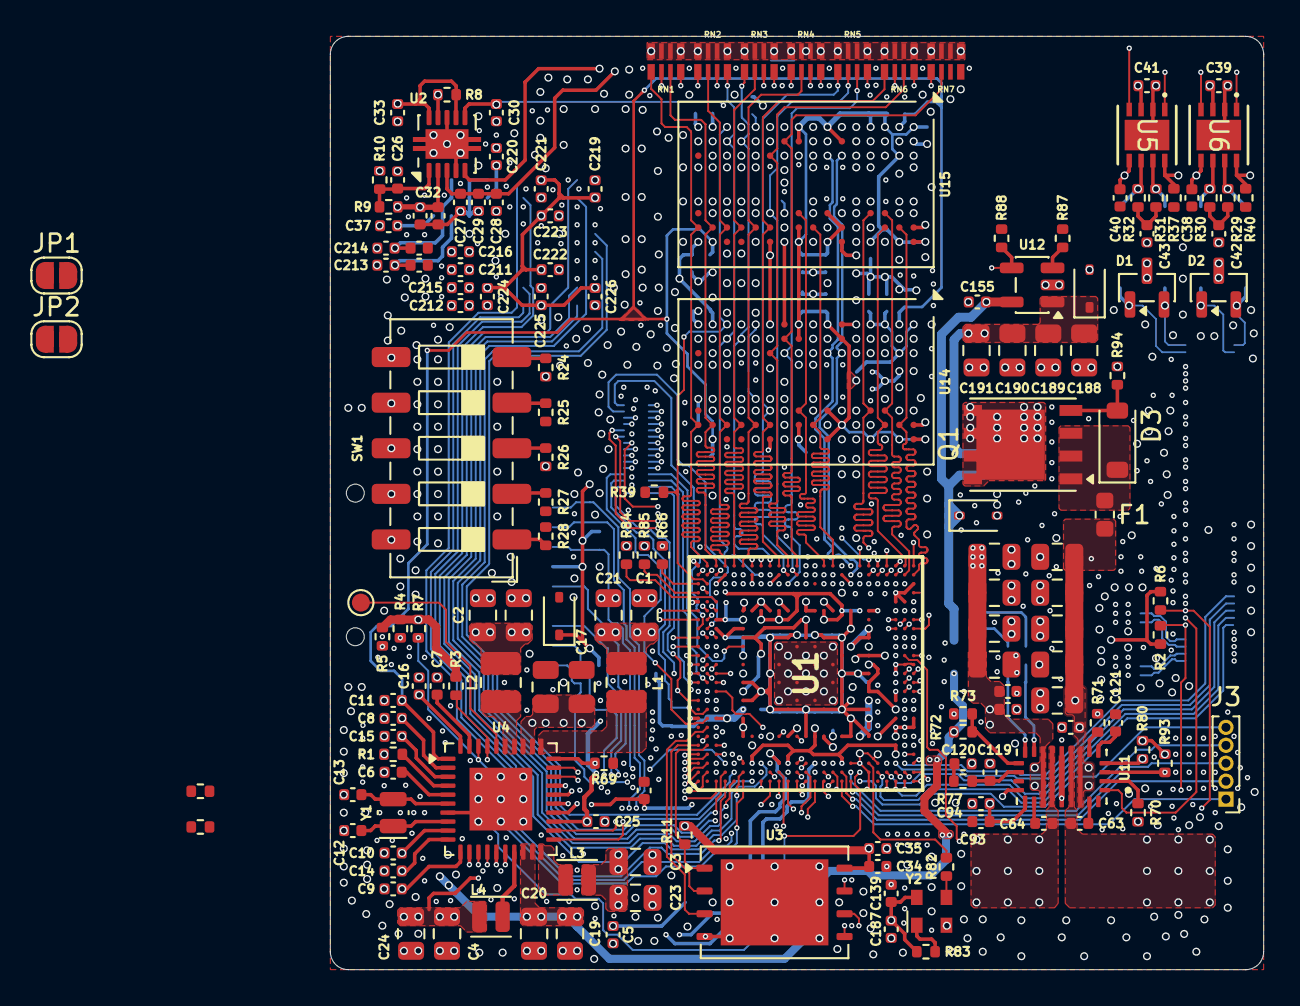
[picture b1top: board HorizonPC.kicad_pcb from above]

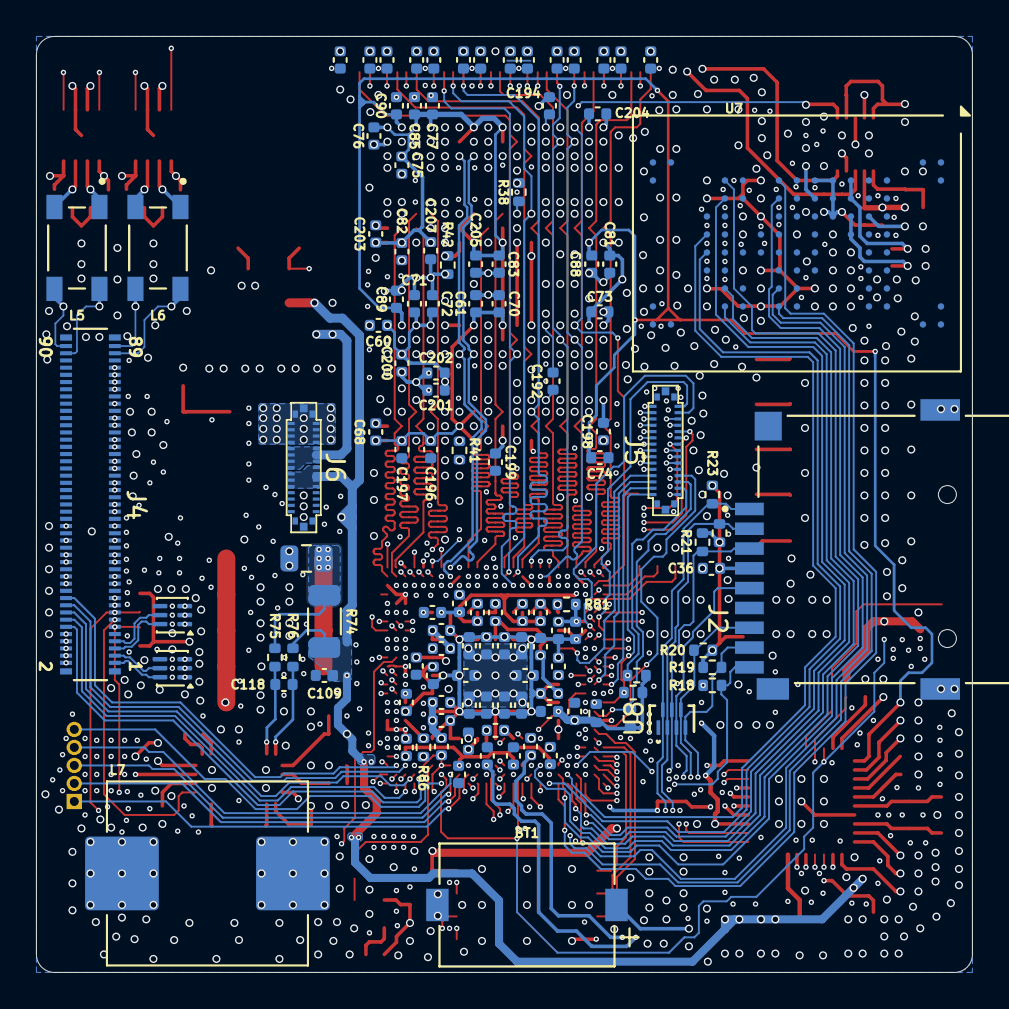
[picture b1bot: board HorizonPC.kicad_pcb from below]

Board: 8 copper layers, 52.0 x 52.0 mm, 280 parts (118 on the bottom side), 245 nets.
